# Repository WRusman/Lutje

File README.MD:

Open-source Battlebot ELRS receiver with 2 built-in ESC's for n20 motors and 2 PWM outputs for external ESC or servo.

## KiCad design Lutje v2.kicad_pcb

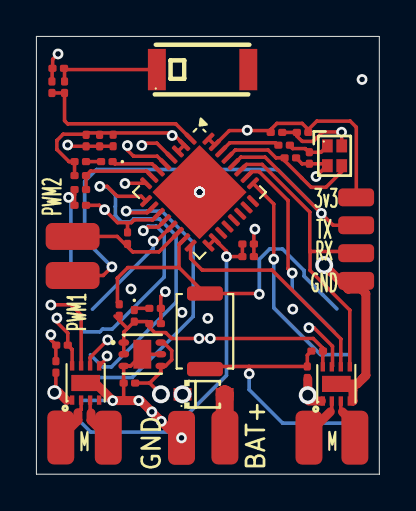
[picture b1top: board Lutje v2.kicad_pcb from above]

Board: 4 copper layers, 19.0 x 24.3 mm, 49 parts (1 on the bottom side), 31 nets.

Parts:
3v3: Conn_01x01_Pin; SolderWirePad_1x01_SMD_1x2mm
BAT+: BAT+; SolderWirePad_1x01_SMD_1.5x3mm
C1, C2, C5: 10uF; C_0201_0603Metric
C3, C11, C14: 100n; C_0201_0603Metric
C4, C8, C10: 1uF; C_0201_0603Metric
C7: 10nF; C_0201_0603Metric
C9: 100nF; C_0201_0603Metric
C12, C13: 1p2; C_0201_0603Metric
C15, C16: 15pF; C_0201_0603Metric
C17, C18, C19, C20: C; C_0201_0603Metric
D1: BAT60A; SOD-323_L1.8-W1.3-LS2.5-RD
D2: PWR; LED_0201_0603Metric
D3: LED; LED_0201_0603Metric
GND: BAT-; SolderWirePad_1x01_SMD_1.5x3mm
GND#2: Conn_01x01_Pin; SolderWirePad_1x01_SMD_1x2mm
J4: M1OUT1; SolderWirePad_1x01_SMD_1.5x3mm
J5: M1OUT2; SolderWirePad_1x01_SMD_1.5x3mm
J6: M2OUT1; SolderWirePad_1x01_SMD_1.5x3mm
J7: M2OUT2; SolderWirePad_1x01_SMD_1.5x3mm
L1: 24nH; L_0201_0603Metric
L2: 2nH; L_0201_0603Metric
L5: SLDA52-2R510G-SITF; ANT-SMD_L5.2-W2.1
PWM1, PWM2: Conn_01x01_Pin; SolderWirePad_1x01_SMD_1.5x3mm
R1, R4: 680R; R_0201_0603Metric
R2, R5: 10K; R_0201_0603Metric
R3: 10k; R_0201_0603Metric
RX: Conn_01x01_Pin; SolderWirePad_1x01_SMD_1x2mm
SW1: BOOT; SW_Push_SPST_NO_Alps_SKRK
TX: Conn_01x01_Pin; SolderWirePad_1x01_SMD_1x2mm
U1, U2: DRV8212PDSGR; WSON-8_L2.0-W2.0-P0.50-TL-EP
U3: ESP32-C3; QFN-32-1EP_5x5mm_P0.5mm_EP3.7x3.7mm
U4: E28-2G4M12S; WIRELM-SMD_E28-2G4M12S
U5: TLV76733DRVR; WSON-6_L2.0-W2.0-P0.65-TL-EP
X1: CJ17-400001010B20; CRYSTAL-SMD_4P-L1.6-W1.2-BL

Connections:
+3V3: 3v3.1 (Pin_1_1), C2.1, C3.2, C4.2, C5.2, C7.1, C8.1, C9.1, C10.1, C11.1, C17.1, C19.1, D2.2 (A), R2.1, R3.1, R4.1, R5.2, U1.8 (VCC), U2.8 (VCC), U3.2 (VDD3P3), U3.3 (VDD3P3), U3.11 (VDD3P3_RTC), U3.17 (VDD3P3_CPU), U3.18 (VDD_SPI), U3.31 (VDDA), U3.32 (VDDA), U4.1 (VCC), U5.1 (OUT), U5.2 (FB/SNS)
/BOOT: R2.2, SW1.2, U3.15 (GPIO9), U4.9 (NRESET)
/BUSY: U3.26 (GPIO19), U4.10 (BUSY)
/CHIP_EN: C14.1, R5.1, U3.7 (CHIP_EN)
/DIO1: U3.25 (GPIO18), U4.11 (DIO1)
/H0_IN1: U1.6 (IN1), U3.4 (XTAL_32K_P)
/H0_IN2: U1.5 (IN2), U3.5 (XTAL_32K_N)
/H0_OUT1: J7.1 (Pin_1_1), U1.2 (OUT1)
/H0_OUT2: J6.1 (Pin_1_1), U1.3 (OUT2)
/H1_IN1: RX.1 (Pin_1_1), U2.5 (IN2), U3.27 (U0RXD)
/H1_IN2: U2.6 (IN1), U3.16 (GPIO10)
/H1_OUT1: J5.1 (Pin_1_1), U2.2 (OUT1)
/H1_OUT2: J4.1 (Pin_1_1), U2.3 (OUT2)
/LED: D3.1 (K), U3.6 (GPIO2)
/MISO: U3.10 (MTDI), U4.3 (MISO_TX)
/MOSI: U3.9 (MTMS), U4.4 (MOSI_RX)
/NSLEEP: U1.7 (nSLEEP), U2.7 (nSLEEP), U3.8 (GPIO3)
/NSS: U3.13 (MTDO), U4.6 (NSS_CTS)
/PWM1: PWM1.1 (Pin_1_1), TX.1 (Pin_1_1), U3.28 (U0TXD)
/PWM2: PWM2.1 (Pin_1_1), R3.2, U3.14 (GPIO8)
/SCK: U3.12 (MTCK), U4.5 (SCK_RTSN)
GND: C1.2, C2.2, C3.1, C4.1, C5.1, C7.2, C8.2, C9.2, C10.2, C11.2, C12.2, C13.2, C14.2, C15.2, C16.2, C17.2, C18.2, C19.2, C20.2, GND.1 (Pin_1_1), GND#2.1 (Pin_1_1), R1.1, SW1.1, U1.4 (GND), U1.9 (EP), U2.4 (GND), U2.9 (EP), U3.33 (GND), U4.2 (GND), U4.7 (GND), U4.8 (GND), U4.14 (GND), U5.3 (GND), U5.5 (GND), U5.7 (EP), X1.2 (GND), X1.4 (GND)
unnamed: C15.1, L1.1, X1.1
unnamed: BAT+.1 (Pin_1_1), D1.2 (A)
unnamed: D2.1 (K), R1.2
unnamed: D3.2 (A), R4.2
unnamed: C13.1, L2.2, L5.1 (FP_1)
unnamed: C12.1, L2.1, U3.1 (LNA_IN)
unnamed: C16.1, U3.29 (XTAL_N), X1.3
unnamed: L1.2, U3.30 (XTAL_P)
VDC: C1.1, C18.1, C20.1, D1.1 (K), U1.1 (VM), U2.1 (VM), U5.4 (EN), U5.6 (IN)

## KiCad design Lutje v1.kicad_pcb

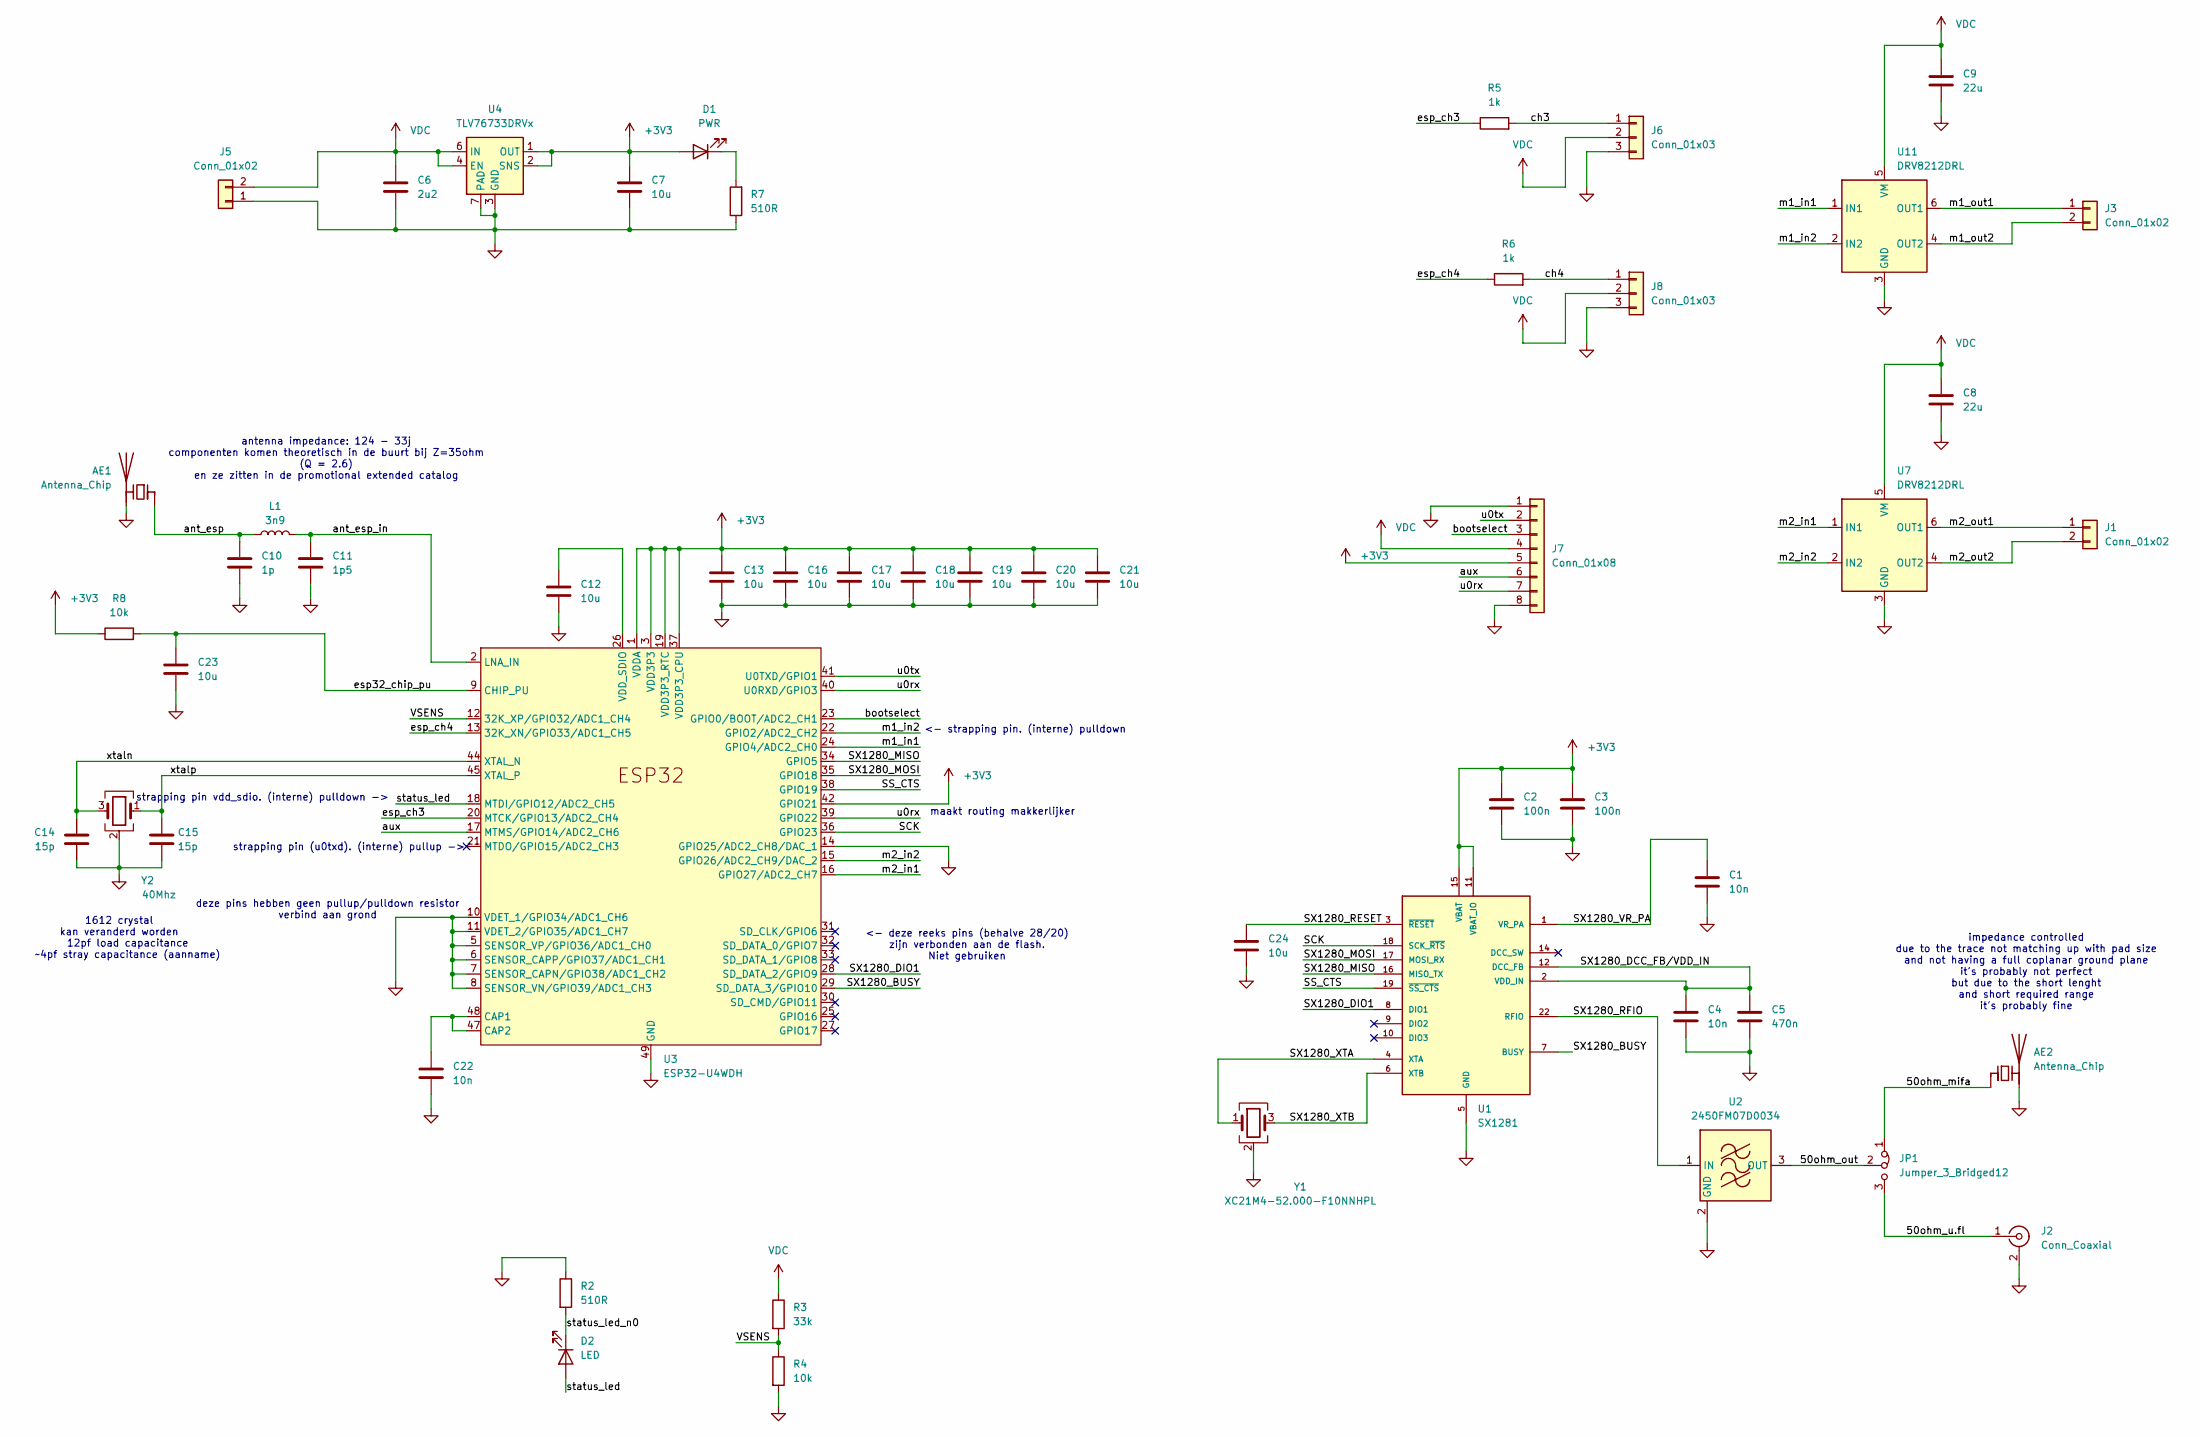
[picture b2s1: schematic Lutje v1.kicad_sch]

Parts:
AE1: Antenna_Chip; KH-3216-H0209; lcsc C2925417
AE2: Antenna_Chip; Texas_SWRA117D_2.4GHz_Right
C1, C4, C22: 10n; C_0402_1005Metric
C2, C3: 100n; C_0402_1005Metric
C5: 470n; C_0402_1005Metric
C6: 2u2; C_0402_1005Metric
C7, C12, C13, C16, C17, C18, C19, C20, C21, C23, C24: 10u; C_0402_1005Metric
C8, C9: 22u; C_0805_2012Metric; lcsc C45783
C10: 1p; C_0402_1005Metric
C11: 1p5; C_0402_1005Metric
C14, C15: 15p; C_0402_1005Metric
D1: PWR; LED_0603_1608Metric
D2: LED; LED_0603_1608Metric
J1, J3: Conn_01x02; PinHeader_1x02_P2.54mm_BIG1
J2: Conn_Coaxial; U.FL_Hirose_U.FL-R-SMT-1_Vertical
J5: Conn_01x02; malenkipower
J6, J8: Conn_01x03; PinHeader_1x03_P2.54mm_Vertical
J7: Conn_01x08; SOIC_clipProgSmall
JP1: Jumper_3_Bridged12; R_0402_jumper_90deg
L1: 3n9; L_0402_1005Metric
R2, R7: 510R; R_0402_1005Metric
R3: 33k; R_0402_1005Metric
R4, R8: 10k; R_0402_1005Metric
R5, R6: 1k; R_0402_1005Metric
U1: SX1281; QFN-24-1EP_4x4mm_P0.5mm_EP2.7x2.7mm; lcsc C2151551
U2: 2450FM07D0034; 2450FM07D0034001T; lcsc C6054595
U3: ESP32-U4WDH; ESP32_QFN-48_vias
U4: TLV76733DRVx; WSON-6-1EP_2x2mm_P0.65mm_EP1x1.6mm
U7, U11: DRV8212DRL; SOT-563; lcsc C3681309
Y1: XC21M4-52.000-F10NNHPL; Crystal_SMD_2016-4Pin_2.0x1.6mm; lcsc C3034316
Y2: 40Mhz; SMD1612_crystal; lcsc C655053

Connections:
+3V3: C2.1, C3.1, C7.1, C13.1, C16.1, C17.1, C18.1, C19.1, C20.1, C21.1, D1.2 (A), J7.5, R8.1, U1.11 (VBAT_IO), U1.15 (VBAT), U3.1 (VDDA), U3.3 (VDD3P3), U3.4 (VDD3P3), U3.19 (VDD3P3_RTC), U3.37 (VDD3P3_CPU), U3.42 (GPIO21), U3.43 (VDDA), U3.46 (VDDA), U4.1 (OUT), U4.2 (SNS)
/50ohm_mifa: AE2.1 (FEED), JP1.1 (A)
/50ohm_out: JP1.2 (C), U2.3 (OUT)
/50ohm_u.fl: J2.1 (In), JP1.3 (B)
/SCK: U1.18 (SCK_~RTS), U3.36 (GPIO23)
/SS_CTS: U1.19 (~SS_CTS), U3.38 (GPIO19)
/SX1280_BUSY: U1.7 (BUSY), U3.29 (SD_DATA_3/GPIO10)
/SX1280_DCC_FB/VDD_IN: C4.1, C5.1, U1.2 (VDD_IN), U1.12 (DCC_FB)
/SX1280_DIO1: U1.8 (DIO1), U3.28 (SD_DATA_2/GPIO9)
/SX1280_MISO: U1.16 (MISO_TX), U3.34 (GPIO5)
/SX1280_MOSI: U1.17 (MOSI_RX), U3.35 (GPIO18)
/SX1280_RESET: C24.1, U1.3 (~RESET)
/SX1280_RFIO: U1.22 (RFIO), U2.1 (IN)
/SX1280_VR_PA: C1.1, U1.1 (VR_PA)
/SX1280_XTA: U1.4 (XTA), Y1.1
/SX1280_XTB: U1.6 (XTB), Y1.3
/VSENS: R3.2, R4.1, U3.12 (32K_XP/GPIO32/ADC1_CH4)
/ant_esp: AE1.1 (FEED), C10.1, L1.1
/ant_esp_in: C11.1, L1.2, U3.2 (LNA_IN)
/aux: J7.6, U3.17 (MTMS/GPIO14/ADC2_CH6)
/bootselect: J7.3, U3.23 (GPIO0/BOOT/ADC2_CH1)
/ch3: J6.1, R5.2
/ch4: J8.1, R6.2
/esp32_chip_pu: C23.1, R8.2, U3.9 (CHIP_PU)
/esp_ch3: R5.1, U3.20 (MTCK/GPIO13/ADC2_CH4)
/esp_ch4: R6.1, U3.13 (32K_XN/GPIO33/ADC1_CH5)
/m1_in1: U3.24 (GPIO4/ADC2_CH0), U11.1 (IN1)
/m1_in2: U3.22 (GPIO2/ADC2_CH2), U11.2 (IN2)
/m1_out1: J3.1, U11.6 (OUT1)
/m1_out2: J3.2, U11.4 (OUT2)
/m2_in1: U3.16 (GPIO27/ADC2_CH7), U7.1 (IN1)
/m2_in2: U3.15 (GPIO26/ADC2_CH9/DAC_2), U7.2 (IN2)
/m2_out1: J1.1, U7.6 (OUT1)
/m2_out2: J1.2, U7.4 (OUT2)
/status_led: D2.2 (A), U3.18 (MTDI/GPIO12/ADC2_CH5)
/status_led_n0: D2.1 (K), R2.2
/u0rx: J7.7, U3.39 (GPIO22), U3.40 (U0RXD/GPIO3)
/u0tx: J7.2, U3.41 (U0TXD/GPIO1)
/xtaln: C14.1, U3.44 (XTAL_N), Y2.3
/xtalp: C15.1, U3.45 (XTAL_P), Y2.1
GND: AE1.2 (PCB_Trace), AE2.2 (PCB_Trace), C1.2, C2.2, C3.2, C4.2, C5.2, C6.2, C7.2, C8.2, C9.2, C10.2, C11.2, C12.2, C13.2, C14.2, C15.2, C16.2, C17.2, C18.2, C19.2, C20.2, C21.2, C22.2, C23.2, C24.2, J2.2 (Ext), J5.1, J6.3, J7.1, J7.8, J8.3, R2.1, R4.2, R7.1, U1.5 (GND), U1.13 (GND), U1.20 (GND), U1.21 (GND), U1.23 (GND), U1.24 (GND), U1.25 (GND), U2.2 (GND), U2.4 (GND), U3.5 (SENSOR_VP/GPIO36/ADC1_CH0), U3.6 (SENSOR_CAPP/GPIO37/ADC1_CH1), U3.7 (SENSOR_CAPN/GPIO38/ADC1_CH2), U3.8 (SENSOR_VN/GPIO39/ADC1_CH3), U3.10 (VDET_1/GPIO34/ADC1_CH6), U3.11 (VDET_2/GPIO35/ADC1_CH7), U3.14 (GPIO25/ADC2_CH8/DAC_1), U3.49 (GND), U4.3 (GND), U4.5 (GND), U4.7 (PAD), U7.3 (GND), U11.3 (GND), Y1.2 (G), Y1.4 (G), Y2.2 (G), Y2.4 (G)
unnamed: D1.1 (K), R7.2
unnamed: C22.1, U3.47 (CAP2), U3.48 (CAP1)
unnamed: C12.1, U3.26 (VDD_SDIO)
VDC: C6.1, C8.1, C9.1, J5.2, J6.2, J7.4, J8.2, R3.1, U4.4 (EN), U4.6 (IN), U7.5 (VM), U11.5 (VM)

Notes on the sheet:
1612 crystal kan veranderd worden
strapping pin (u0txd). (interne) pullup ->
12pf load capacitance ~4pf stray capacitance (aanname)
deze pins hebben geen pullup/pulldown resistor verbind aan grond
maakt routing makkerlijker
<- strapping pin. (interne) pulldown
strapping pin vdd_sdio. (interne) pulldown ->
antenna impedance: 124 - 33j componenten komen theoretisch in de buurt bij Z=35ohm (Q = 2.6) en ze zitten in de promotional extended catalog
impedance controlled due to the trace not matching up with pad size and not having a full coplanar ground plane it's probably not perfect but due to the short lenght and short required range it's probably fine
<- deze reeks pins (behalve 28/20) zijn verbonden aan de flash. Niet gebruiken

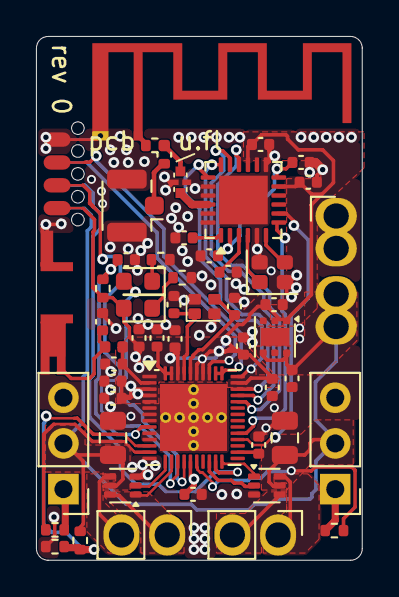
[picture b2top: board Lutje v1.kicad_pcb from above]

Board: 4 copper layers, 18.1 x 29.1 mm, 52 parts (1 on the bottom side), 45 nets.
